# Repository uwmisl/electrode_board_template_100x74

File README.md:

# electrode_board_template_100x74

This project provides a KiCad template project which can be used as a convenient
starting point for custom electrode boards. It includes connector footprints, 
placed at the correct locations, as well as the "standard" mounting hole placements
used by some other components. 

## Installation

To install the template, check out the project and place it into your 
KiCad user template directory. The location of this directory varies on 
different operating systems, but you can find it by runnign KiCad and selecting
"Preferences->Configure Paths..." in the menu. You are looking for the value of
`KICAD_USER_TEMPLATE_DIR`. On linux or MacOS, this is likely to be `$HOME/kicad/template`.

So, for example:

```
mkdir -p ~/kicad/template
cd ~/kicad/template
git clone https://github.com/uwmisl/electrode_board_template_100x74
```

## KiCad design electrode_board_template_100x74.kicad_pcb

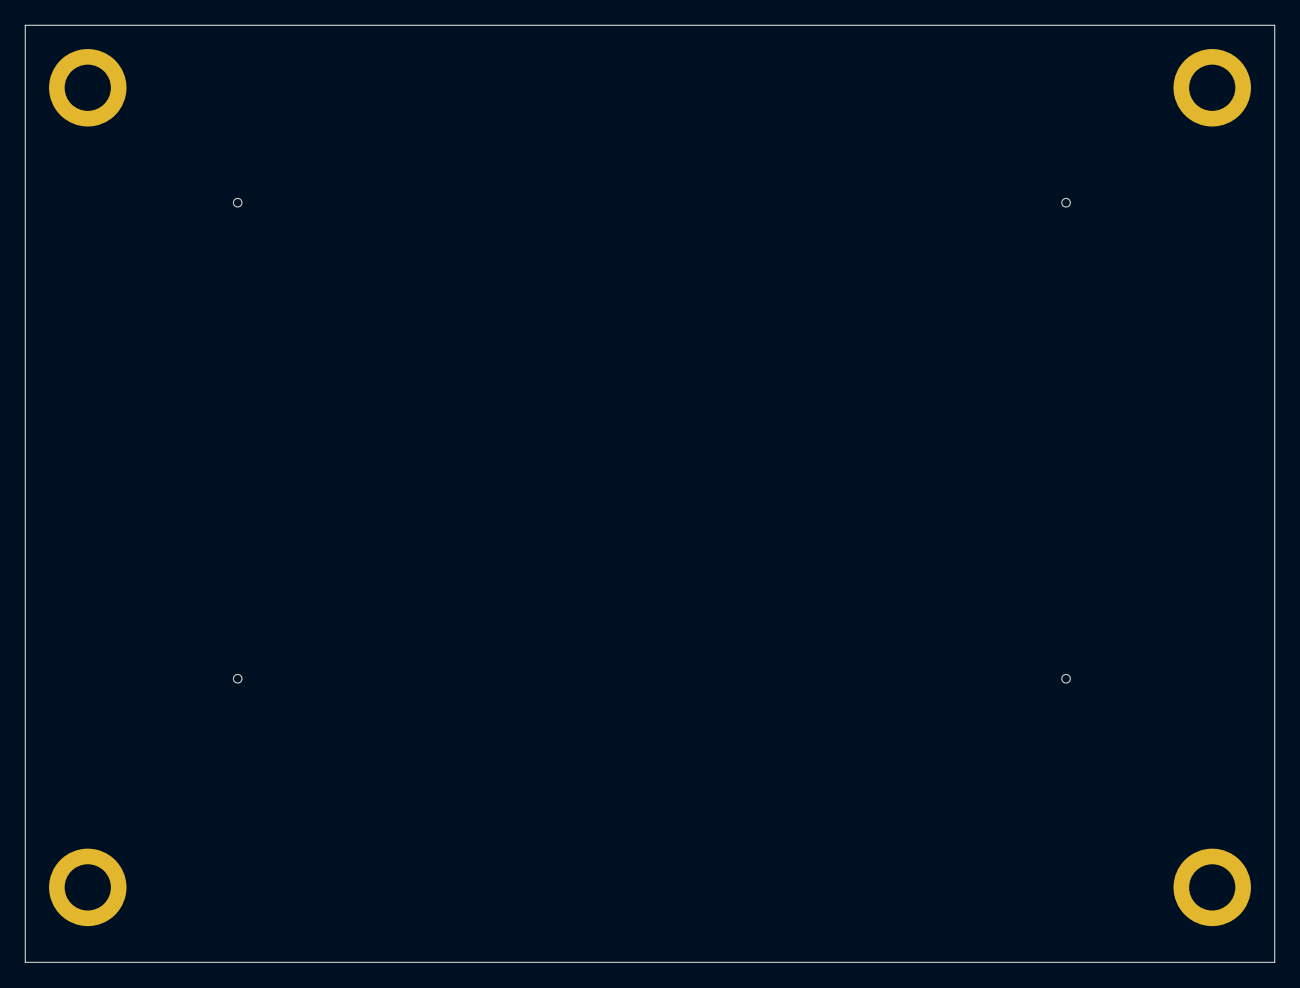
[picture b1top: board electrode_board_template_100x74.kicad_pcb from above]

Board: 2 copper layers, 100.0 x 75.0 mm, 7 parts (1 on the bottom side), 2 nets, no tracks yet.

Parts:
H1, H2, H3, H4: MountingHole_Pad; Keystone-4929
J1, J2: Conn_02x32_Odd_Even; CLP-132-02-F-D
J11: TopPlate; Header1_RA

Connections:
/P97: J1.36, J11.1
/POUR: H1.1, H2.1, H3.1, H4.1

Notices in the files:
parts and their libraries:
Copyright 2016 Accelerated Designs. All rights reserved.
